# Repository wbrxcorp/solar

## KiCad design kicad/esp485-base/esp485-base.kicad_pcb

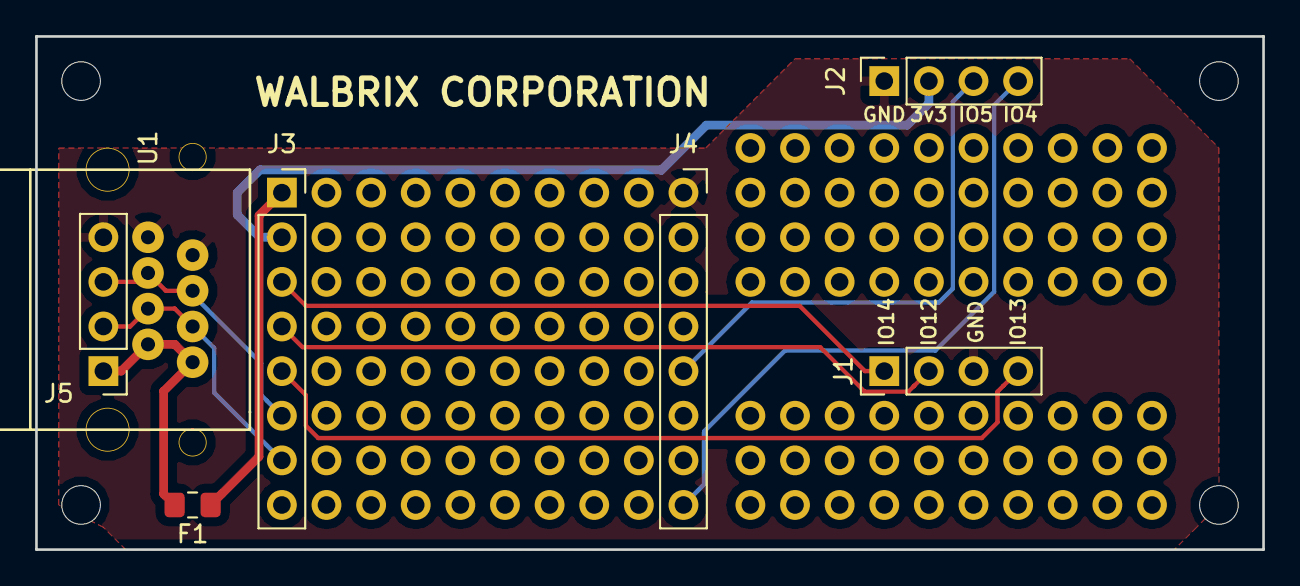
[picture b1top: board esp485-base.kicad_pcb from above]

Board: 2 copper layers, 69.9 x 29.2 mm, 7 parts (0 on the bottom side), 11 nets.

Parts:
F1: Fuse; Fuse_0805_2012Metric_Pad1.15x1.40mm_HandSolder
J1, J5: Conn_01x04; PinHeader_1x04_P2.54mm_Vertical
J2: Conn_01x04; PinSocket_1x04_P2.54mm_Vertical
J3, J4: Conn_01x08; PinSocket_1x08_P2.54mm_Vertical
U1: 7810-8P8C

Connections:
+3V3: J2.2, J3.2
A: J3.6, J5.3, U1.5, U1.6
B: J3.7, J5.2, U1.3, U1.4
GND: J1.3, J2.1, J4.1, J5.4, U1.7, U1.8
IO4: J2.4, J4.8
IO5: J2.3, J4.5
IO12: J1.2, J3.4
IO13: J1.4, J3.5
IO14: J1.1, J3.3
VCC: F1.2, J5.1, U1.1, U1.2
VIN: F1.1, J3.1

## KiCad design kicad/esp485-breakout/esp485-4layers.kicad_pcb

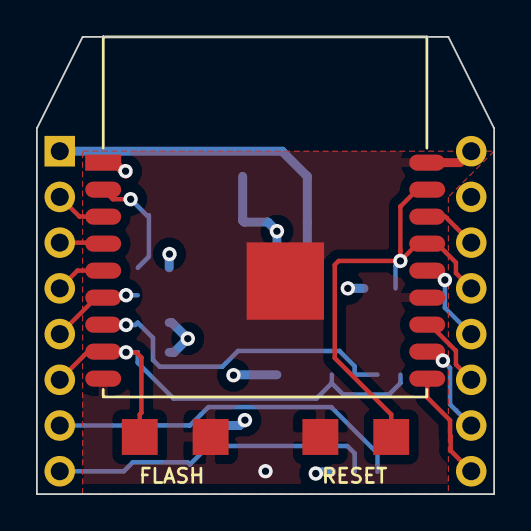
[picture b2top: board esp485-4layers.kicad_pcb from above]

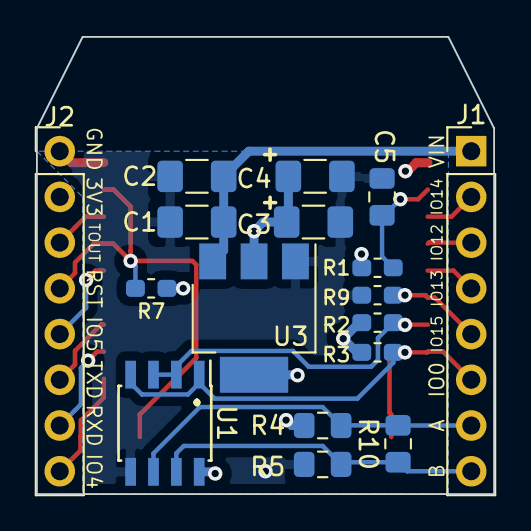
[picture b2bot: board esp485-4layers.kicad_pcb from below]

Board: 4 copper layers, 25.4 x 25.4 mm, 20 parts (17 on the bottom side), 18 nets.

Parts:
C1, C2, C3, C4: C; C_1206_3216Metric_Pad1.42x1.75mm_HandSolder
C5: C; C_0805_2012Metric_Pad1.15x1.40mm_HandSolder
J1, J2: Conn_01x08; PinHeader_1x08_P2.54mm_Vertical
R1, R2, R3, R7, R9: 10K; R_0603_1608Metric_Pad1.05x0.95mm_HandSolder
R4, R5: 20K; R_0805_2012Metric_Pad1.15x1.40mm_HandSolder
R10: 100; R_0805_2012Metric_Pad1.15x1.40mm_HandSolder
SW1, SW2: SW_Push; tactile_switch_smd_4x3mm_2p
U1: MAX3485; SOIC-8_3.9x4.9mm_P1.27mm
U2: ESP-WROOM-02; ESP-13-WROOM-02
U3: AMS1117-3.3; SOT-223-3_TabPin2

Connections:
+3V3: C3.1, C4.1, J2.2, R1.1, R2.2, R3.2, R4.1, R7.1, U1.8, U2.1, U3.2
/A: J1.7, R4.2, R10.2, U1.6
/B: J1.8, R5.1, R10.1, U1.7
/EN: C5.1, R1.2, U2.2
/IO0: J1.6, R3.1, SW1.1, U1.1, U1.4, U2.8
/IO2: R2.1, U1.2, U1.3, U2.7
/IO4: J2.8, U2.10
/IO5: J2.5, U2.14
/IO12: J1.3, U2.4
/IO13: J1.4, U2.5
/IO14: J1.2, U2.3
/IO15: J1.5, R9.1, U2.6
/RST: J2.4, R7.2, SW2.1, U2.15, U2.17
/RXD: J2.7, U2.11
/TOUT: J2.3, U2.16
/TXD: J2.6, U2.12
GND: C1.2, C2.2, C3.2, C4.2, C5.2, J2.1, R5.2, R9.2, SW1.2, SW2.2, U1.5, U2.9, U2.13, U2.18, U2.PAD, U3.1
VCC: C1.1, C2.1, J1.1, U3.3

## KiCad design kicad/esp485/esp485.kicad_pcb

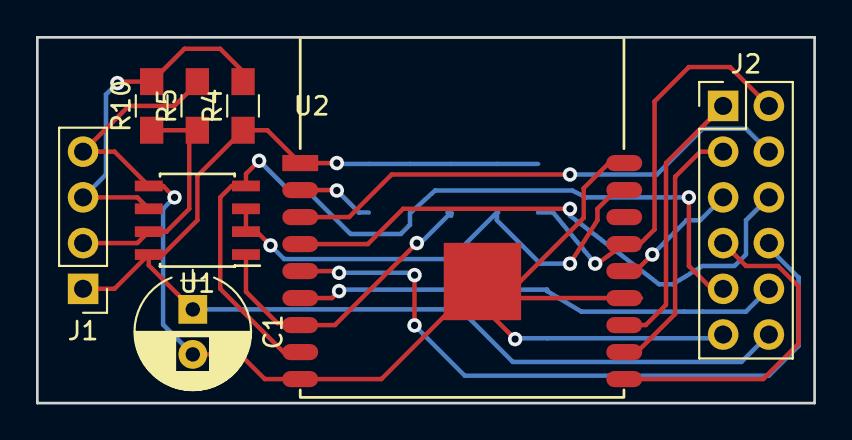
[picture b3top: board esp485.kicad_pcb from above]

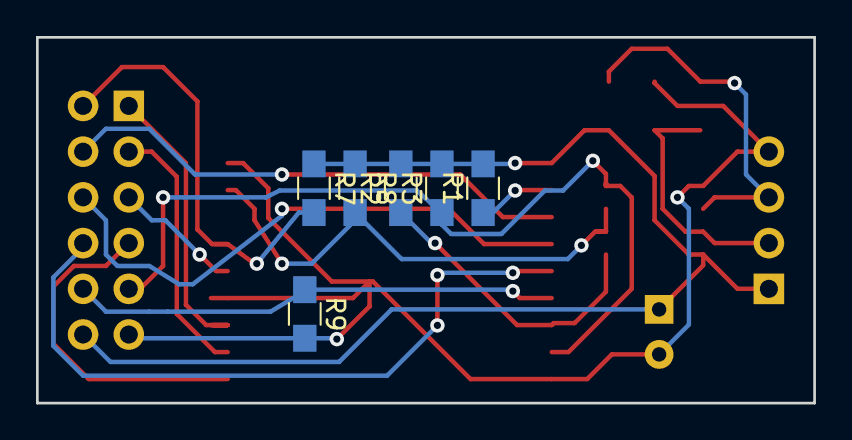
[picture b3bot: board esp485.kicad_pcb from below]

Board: 2 copper layers, 43.2 x 20.3 mm, 14 parts (6 on the bottom side), 17 nets.

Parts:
C1: CP; CP_Radial_D6.3mm_P2.50mm
J1: Conn_01x04; Pin_Header_Straight_1x04_Pitch2.54mm
J2: Conn_02x06_Odd_Even; Pin_Header_Straight_2x06_Pitch2.54mm
R1, R2, R3, R7, R8, R9: 10K; R_0805_HandSoldering
R4, R5: 20K; R_0805_HandSoldering
R10: 100; R_0805_HandSoldering
U1: MAX3485; SOIC-8_3.9x4.9mm_Pitch1.27mm
U2: ESP-WROOM-02; ESP-13-WROOM-02

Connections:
+3V3: C1.1, J1.1, J2.12, R1.2, R2.2, R3.2, R4.1, R7.1, R8.1, U1.8, U2.1
GND: C1.2, J1.4, J2.11, R5.2, R9.2, U1.5, U2.9, U2.13, U2.18, U2.PAD
unnamed: J1.2, R5.1, R10.1, U1.7
unnamed: J1.3, R4.2, R10.2, U1.6
unnamed: J2.1, U2.12
unnamed: J2.2, R7.2, U2.15
unnamed: J2.3, U2.11
unnamed: J2.4, U2.3
unnamed: J2.5, U2.14
unnamed: J2.6, U2.4
unnamed: J2.7, U2.10
unnamed: J2.8, U2.5
unnamed: J2.9, R3.1, U1.4, U2.8
unnamed: J2.10, R9.1, U2.6
unnamed: R1.1, U2.2
unnamed: R2.1, U1.1, U2.7
unnamed: R8.2, U1.2, U1.3, U2.17

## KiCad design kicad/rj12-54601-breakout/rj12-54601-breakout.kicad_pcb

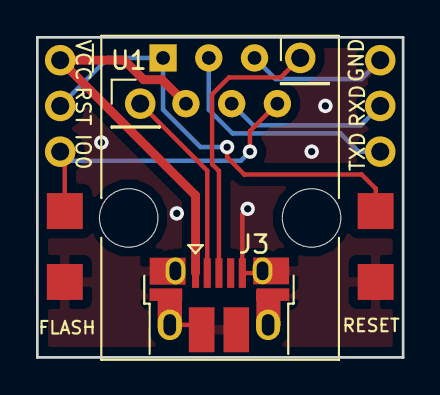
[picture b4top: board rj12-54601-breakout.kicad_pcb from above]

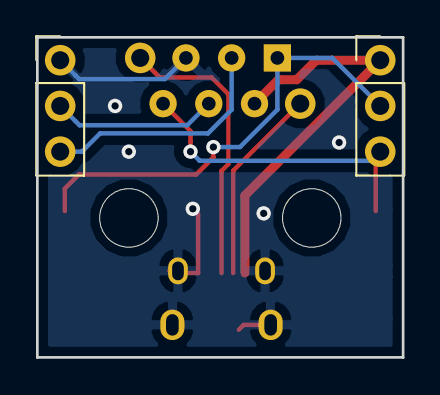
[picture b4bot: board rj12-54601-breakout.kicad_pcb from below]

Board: 2 copper layers, 20.3 x 17.8 mm, 8 parts (2 on the bottom side), 8 nets.

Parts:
J1, J2: Conn_01x03; PinHeader_1x03_P2.54mm_Vertical
J3: USB_B_Micro; USB_Micro-B_Amphenol_10103594-0001LF_Horizontal
J4, J5: Conn_01x01_Female; PinHeader_1x01_P2.54mm_Vertical
SW1, SW2: SW_Push; tactile_switch_smd_4x3mm_2p
U1: RJ12; RJ12_Amphenol_54601

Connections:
/D+: J3.3, J4.1
/D-: J3.2, J5.1
/IO0: J1.3, SW1.1, U1.6
/RESET: J1.2, SW2.1, U1.1
/RXD: J2.2, U1.4
/TXD: J2.3, U1.3
GND: J2.1, J3.5, J3.6, SW1.2, SW2.2, U1.5
VCC: J1.1, J3.1, U1.2

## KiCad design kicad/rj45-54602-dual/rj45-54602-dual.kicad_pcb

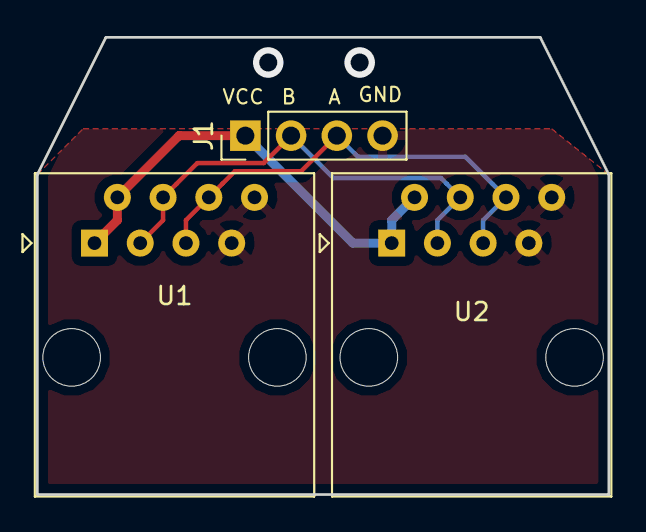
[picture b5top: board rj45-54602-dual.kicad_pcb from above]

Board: 2 copper layers, 31.8 x 25.4 mm, 3 parts (0 on the bottom side), 4 nets.

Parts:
J1: Conn_01x04; PinHeader_1x04_P2.54mm_Vertical
U1, U2: RJ45; RJ45_Amphenol_54602-x08_Horizontal

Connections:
/A: J1.3, U1.5, U1.6, U2.5, U2.6
/B: J1.2, U1.3, U1.4, U2.3, U2.4
GND: J1.4, U1.7, U1.8, U2.7, U2.8
VCC: J1.1, U1.1, U1.2, U2.1, U2.2
